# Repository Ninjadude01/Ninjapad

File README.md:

# Ninjapad

Ninjapad is a custom 5-key macropad that is fully customizable using qmk software. It uses cherry mx switches, a xiao rp 2040, and a custom PCB! I decided to make this macropad because I spend lots of my day on my computer, and having a customizable tool would be very useful and time saving. Additionally, it is a great project to help intoduce me to qmk and soldering, as I plan to make a full keyboard in the near future :)

IRL Photos:

Here is my project in fusion:

Here is the schematic diagram:

Here is the PCB layout:

BOM:

|Item|Part Name       |Quantity|Description                 |Cost |Link                                                                                                                                                                                                                                                                                                                                                                                                                                                                                                                                                                                                                                                                  |
|----|----------------|--------|----------------------------|-----|----------------------------------------------------------------------------------------------------------------------------------------------------------------------------------------------------------------------------------------------------------------------------------------------------------------------------------------------------------------------------------------------------------------------------------------------------------------------------------------------------------------------------------------------------------------------------------------------------------------------------------------------------------------------|
|1   |PCB             |5       |Custom Printed Circuit Board|$1.99|https://jlcpcb.com/                                                                                                                                                                                                                                                                                                                                                                                                                                                                                                                                                                                                                                                   |
|2   |Cherry mx Switch|10      |Keyboard Switch             |$7.57|https://www.aliexpress.com/item/1005008811335051.html?spm=a2g0o.cart.0.0.6df938dabXCDew&mp=1&pdp_npi=6%40dis%21CAD%21CAD%2052.73%21CAD%2045.79%21%21CAD%2044.15%21%21%21%40210328df17740487064442830e3672%2112000046764301536%21ct%21CA%217451194651%21%211%210%21                                                                                                                                                                                                                                                                                                                                                                                                    |
|3   |Cherry mx Keycap|5       |Keycap                      |$4.03|https://www.aliexpress.com/item/1005008795444732.html?spm=a2g0o.productlist.main.3.4ba1nQTEnQTEAd&algo_pvid=f2a257d6-f6ba-4a56-844c-46b02c23fcf6&algo_exp_id=f2a257d6-f6ba-4a56-844c-46b02c23fcf6-2&pdp_ext_f=%7B%22order%22%3A%22687%22%2C%22eval%22%3A%221%22%2C%22fromPage%22%3A%22search%22%7D&pdp_npi=6%40dis%21CAD%215.69%211.60%21%21%214.05%211.14%21%402101f70717740488092483736e5c9e%2112000046697462916%21sea%21CA%217451194651%21ABX%211%210%21n_tag%3A-29910%3Bd%3A8fd05d1b%3Bm03_new_user%3A-29895%3BpisId%3A5000000197831899&curPageLogUid=ol1gduKDApl2&utparam-url=scene%3Asearch%7Cquery_from%3A%7Cx_object_id%3A1005008795444732%7C_p_origin_prod%3A|

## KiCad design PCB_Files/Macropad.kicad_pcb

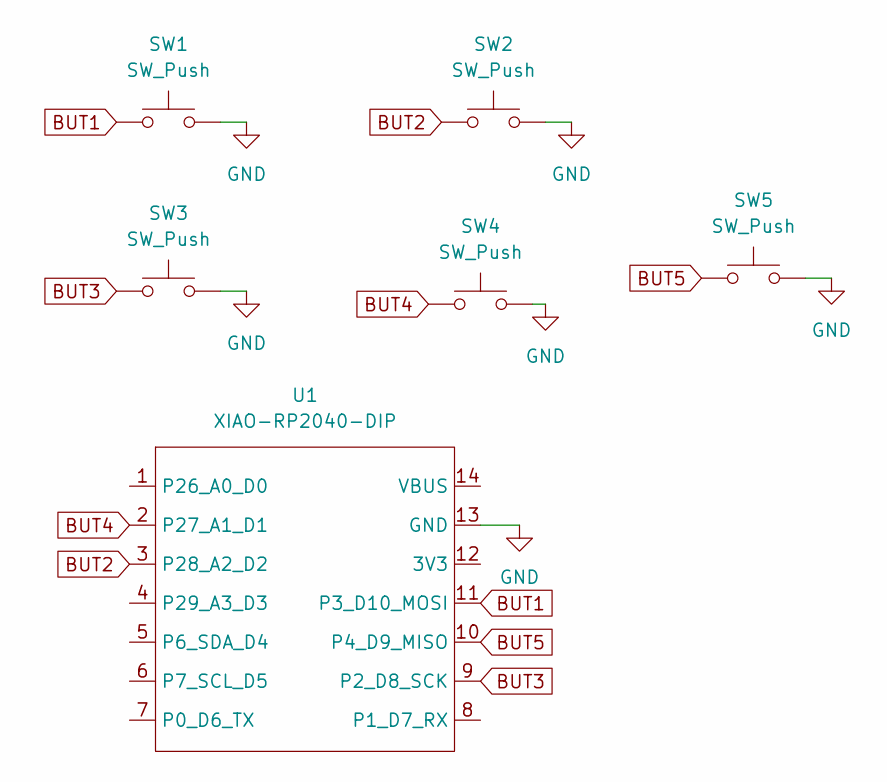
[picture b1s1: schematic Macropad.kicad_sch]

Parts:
SW1, SW2, SW3, SW4, SW5: SW_Push; SW_Cherry_MX_1.00u_PCB
U1: XIAO-RP2040-DIP

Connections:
BUT1: SW1.1, U1.11 (P3_D10_MOSI)
BUT2: SW2.1, U1.3 (P28_A2_D2)
BUT3: SW3.1, U1.9 (P2_D8_SCK)
BUT4: SW4.1, U1.2 (P27_A1_D1)
BUT5: SW5.1, U1.10 (P4_D9_MISO)
GND: SW1.2, SW2.2, SW3.2, SW4.2, SW5.2, U1.13 (GND)

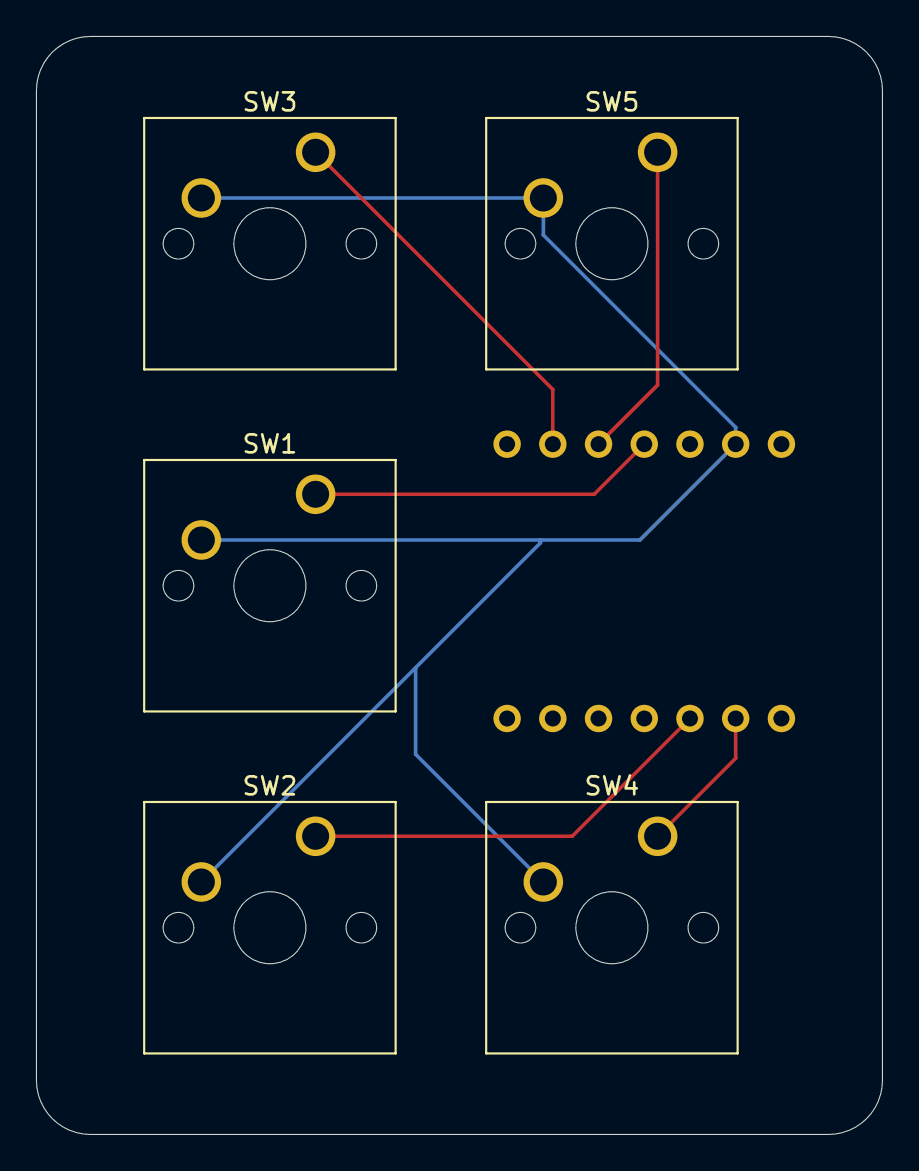
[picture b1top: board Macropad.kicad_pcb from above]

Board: 2 copper layers, 47.0 x 61.0 mm, 6 parts (1 on the bottom side), 6 nets.

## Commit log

2026-03-30 Create temp
2026-03-30 Create PCB_Files
2026-03-30 Create tmep
